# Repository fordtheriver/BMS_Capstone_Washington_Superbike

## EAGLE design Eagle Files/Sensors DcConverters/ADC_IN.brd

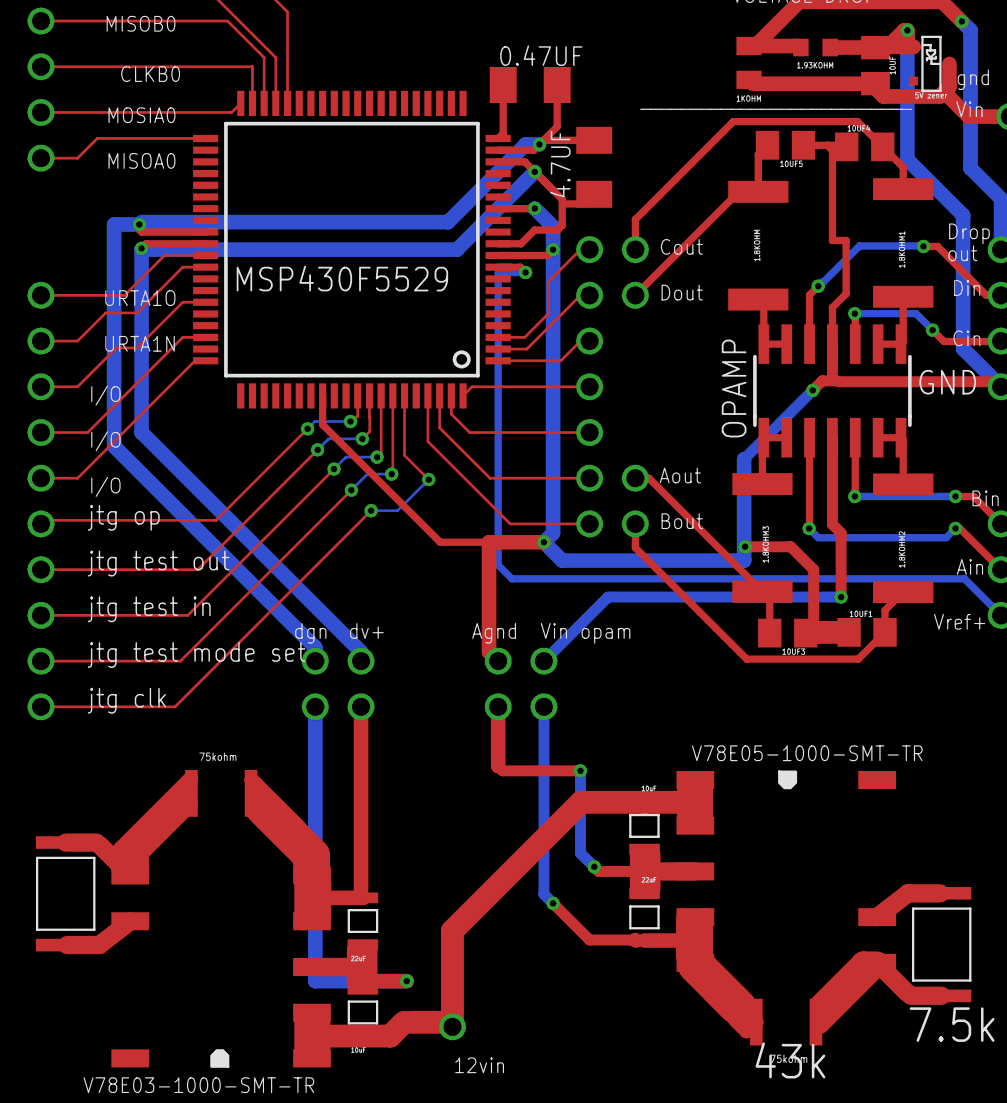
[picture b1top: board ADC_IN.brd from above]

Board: 2 copper layers, 26 parts (0 on the bottom side), 20 nets.

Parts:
0.47UF, 4.7UF: C1206K
1.8KOHM, 1.8KOHM1, 1.8KOHM2, 1.8KOHM3: R2512
1.93KOHM: R0603
1KOHM: R0805
10UF, 10UF1, 10UF3, 10UF4, 10UF5: C0805K
E$1: PLVA650A,215
E$2, E$8: ESR25JZPF7502
E$3, E$9: CRGP2512F22K
E$4, E$10: GRT31CR61H106KE01L
E$5, E$11: GRT31CC81C226KE01L
E$6: V78E05-1000-SMT-TR
E$7: V78E03-1000-SMT-TR
MSP430F5529: QFP80_SOT496-1
OPAMP: SO14

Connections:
S$1: 1.8KOHM.2, OPAMP.13, OPAMP.14
S$2: 1.8KOHM1.2, OPAMP.8, OPAMP.9
S$3: 1.8KOHM2.2, 10UF1.2
S$4: 1.8KOHM2.1, OPAMP.6, OPAMP.7
S$5: 1.8KOHM.1, 10UF5.2
S$7: MSP430F5529.41, MSP430F5529.42, MSP430F5529.43, MSP430F5529.45, MSP430F5529.46, MSP430F5529.47, MSP430F5529.48
S$8: 0.47UF.1, 0.47UF.2, 1.93KOHM.1, 4.7UF.1, 4.7UF.2, 10UF.1, 10UF1.1, 10UF3.1, 10UF4.1, 10UF5.1, E$1.1, E$7.VOUT_1, E$7.VOUT_2, E$8.P$2, E$11.P$1, MSP430F5529.1, MSP430F5529.2, MSP430F5529.3, MSP430F5529.4, MSP430F5529.5, MSP430F5529.6, MSP430F5529.7, MSP430F5529.8, MSP430F5529.9, MSP430F5529.10, MSP430F5529.11, MSP430F5529.12, MSP430F5529.13, MSP430F5529.14, MSP430F5529.15, MSP430F5529.16, MSP430F5529.17, MSP430F5529.18, MSP430F5529.19, MSP430F5529.20, MSP430F5529.21, MSP430F5529.22, MSP430F5529.23, MSP430F5529.24, MSP430F5529.25, MSP430F5529.26, MSP430F5529.27, MSP430F5529.28, MSP430F5529.29, MSP430F5529.30, MSP430F5529.31, MSP430F5529.32, MSP430F5529.33, MSP430F5529.34, MSP430F5529.35, MSP430F5529.36, MSP430F5529.37, MSP430F5529.38, MSP430F5529.39, MSP430F5529.40, MSP430F5529.49, MSP430F5529.50, MSP430F5529.51, MSP430F5529.52, MSP430F5529.53, MSP430F5529.54, MSP430F5529.55, MSP430F5529.56, MSP430F5529.57, MSP430F5529.58, MSP430F5529.59, MSP430F5529.60, MSP430F5529.61, MSP430F5529.62, MSP430F5529.63, MSP430F5529.64, MSP430F5529.65, MSP430F5529.66, MSP430F5529.67, MSP430F5529.68, MSP430F5529.69, MSP430F5529.70, MSP430F5529.71, MSP430F5529.72, MSP430F5529.73, MSP430F5529.74, MSP430F5529.75, MSP430F5529.76, MSP430F5529.77, MSP430F5529.78, MSP430F5529.79, MSP430F5529.80, OPAMP.11
S$9: 1.8KOHM3.1, OPAMP.1, OPAMP.2
S$10: 1.8KOHM1.1, 10UF4.2
S$11: 1.8KOHM3.2, 10UF3.2
S$12: E$4.P$1, E$5.P$2, E$6.GND_2
S$16: E$7.GND_2, E$10.P$1, E$11.P$2
S$17: 1.93KOHM.2, 1KOHM.1
S$19: E$7.VADJ, E$8.P$1, E$9.P$2
S$20: 1KOHM.2, 10UF.2, E$1.3
S$24: E$2.P$1, E$3.P$2, E$6.VADJ
S$25: E$3.P$1, E$6.GND_1
S$29: E$7.GND_1, E$9.P$1
S$30: E$4.P$2, E$6.VIN_1, E$6.VIN_2, E$7.VIN_1, E$7.VIN_2, E$10.P$2
S$32: E$2.P$2, E$5.P$1, E$6.VOUT_1, E$6.VOUT_2
